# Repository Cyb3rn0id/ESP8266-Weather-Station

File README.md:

# ESP8266 Simple Weather Station

This is a simple Wi-Fi Weather Station based on a NodeMCU (ESP8266).  
It Shows Temperature, Humidity, Heat Index, Pressure, Altitude, Minimum and Maxim Temperatures on a display and on a remote device.  
I made 2 versions:  
- Server version (you connect cirectly to station IP address)
- MQTT version (you need an MQTT Broker and a system for visualize data: I use a Raspberry Pi with Mosquitto and NodeRed)

## Sensors used
- DHT22 for Temperature and Humidity
- BME280 for atmosferic pressure

In the picture I've enclosed circuit and a little 220V->5V switching PSU in an IP56 external box with transparent lid: it's made by Gewiss and box code is GW 44 426

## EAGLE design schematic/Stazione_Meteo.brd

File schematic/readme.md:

Schematic (use Eagle 8.0)
for Node MCU used please refer to my repository "Eagle Libraries"

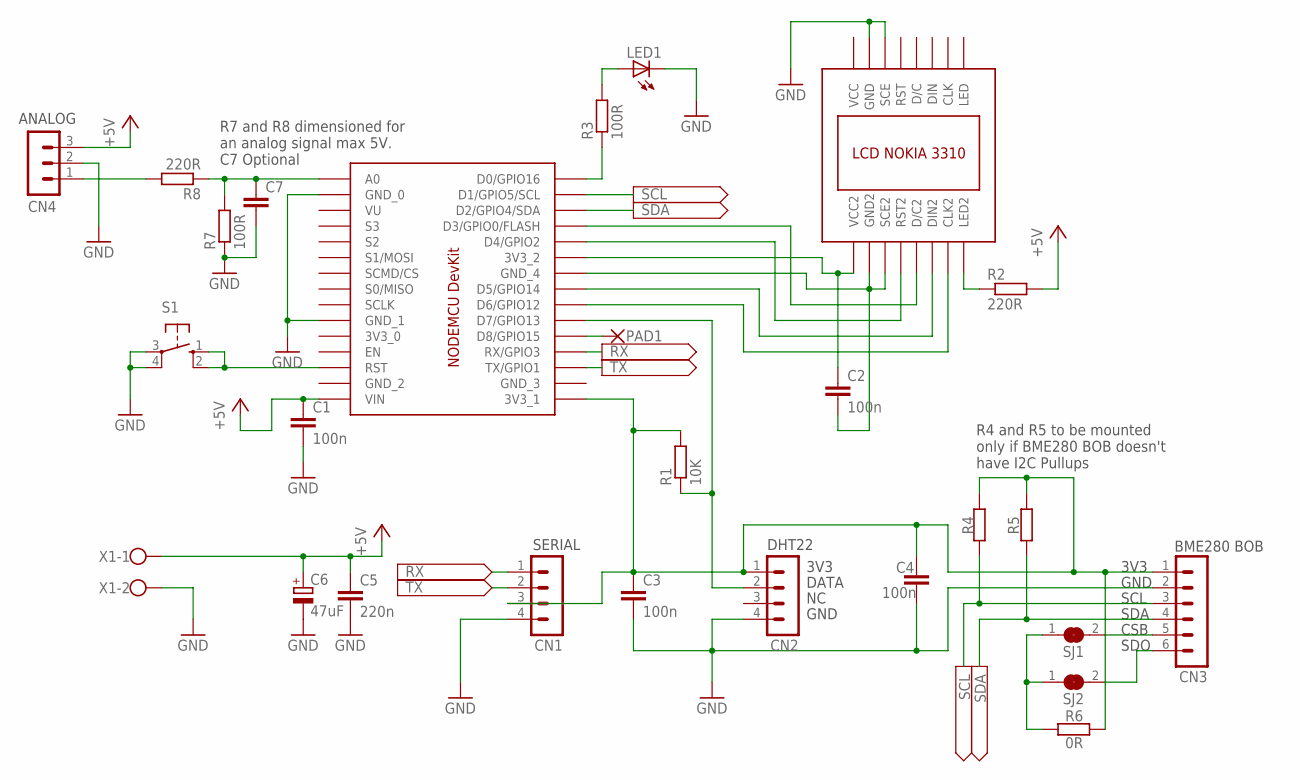
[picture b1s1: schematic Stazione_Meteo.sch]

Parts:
C1, C2, C3, C4: 100n; C025-024X044
C5: 220n; C025-024X044
C6: 47uF; E2,5-6E
C7: C-EU025-024X044; C025-024X044
CN1, CN2: MA04-1
CN3: MA06-1
CN4: MA03-1
LED1: LED5MM
PAD1: 1,6/0,9
R1: 10K; 0204/7
R2, R8: 220R; 0204/7
R3, R7: 100R; 0204/7
R4, R5: R-EU_0204/7; 0204/7
R6: 0R; 0204/7
S1: 10-XX; B3F-10XX
SJ1, SJ2: SJ
U$1: NODEMCU_DEVKIT
U$2: NOKIA_3310/5110_BOB
X1: W237-102

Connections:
3V3_0: U$1.3V3_0
+5V: C1.1, C5.1, C6.+, CN4.3, R2.2, U$1.VIN, X1.1
GND: C1.2, C3.2, C4.2, C5.2, C6.-, C7.2, CN1.4, CN2.4, CN3.2, CN4.2, LED1.K (C), R7.1, S1.3, S1.4 (P1), U$1.GND0 (GND_0), U$1.GND1 (GND_1), U$2.GND, U$2.SCE, X1.2
GND_2: U$1.GND2 (GND_2)
GND_3: U$1.GND3 (GND_3)
LED: U$2.LED
unnamed: R3.1, U$1.D0/GPIO16
unnamed: LED1.A, R3.2
unnamed: CN2.2, R1.1, U$1.D7/GPIO13
unnamed: S1.1 (S), S1.2 (S1), U$1.RST
unnamed: R2.1, U$2.LED2
unnamed: U$1.D5/GPIO14, U$2.DIN2
unnamed: U$1.D3/GPIO0 (D3/GPIO0/FLASH), U$2.D/C2
unnamed: U$1.D4/GPIO2, U$2.RST2
unnamed: C2.1, U$1.3V3_2, U$2.VCC2
unnamed: U$1.D6/GPIO12, U$2.CLK2
unnamed: R6.2, SJ1.1, SJ2.1
unnamed: C2.2, U$1.GND4 (GND_4), U$2.GND2, U$2.SCE2
unnamed: PAD1.1, U$1.D8/GPIO15
unnamed: CN3.5, SJ1.2
unnamed: CN3.6, SJ2.2
unnamed: C3.1, C4.1, CN1.3, CN2.1, CN3.1, R1.2, R4.2, R5.2, R6.1, U$1.3V3_1
unnamed: CN4.1, R8.2
unnamed: C7.1, R7.2, R8.1, U$1.A0
RX: CN1.1, U$1.RX/GPIO3
SCL: CN3.3, R4.1, U$1.D1/GPIO5 (D1/GPIO5/SCL)
SDA: CN3.4, R5.1, U$1.D2/GPIO4 (D2/GPIO4/SDA)
TX: CN1.2, U$1.TX/GPIO1
VCC: U$2.VCC

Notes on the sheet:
3V3
DATA
GND
DHT22
SCL
SDA
BME280 BOB
CSB
SDO
SERIAL
R4 and R5 to be mounted only if BME280 BOB doesn't have I2C Pullups
R7 and R8 dimensioned for an analog signal max 5V. C7 Optional
ANALOG

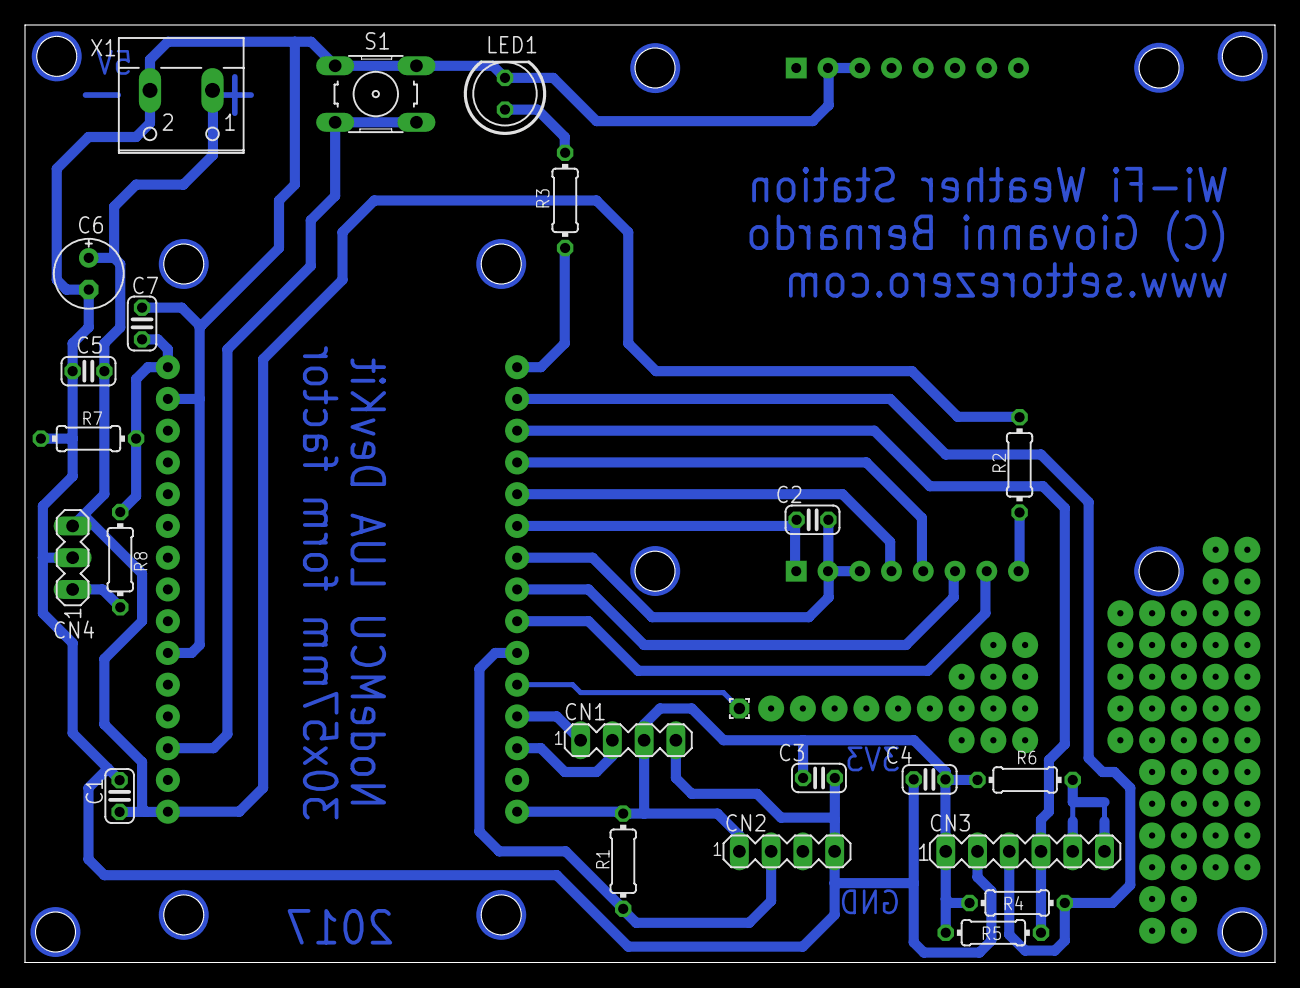
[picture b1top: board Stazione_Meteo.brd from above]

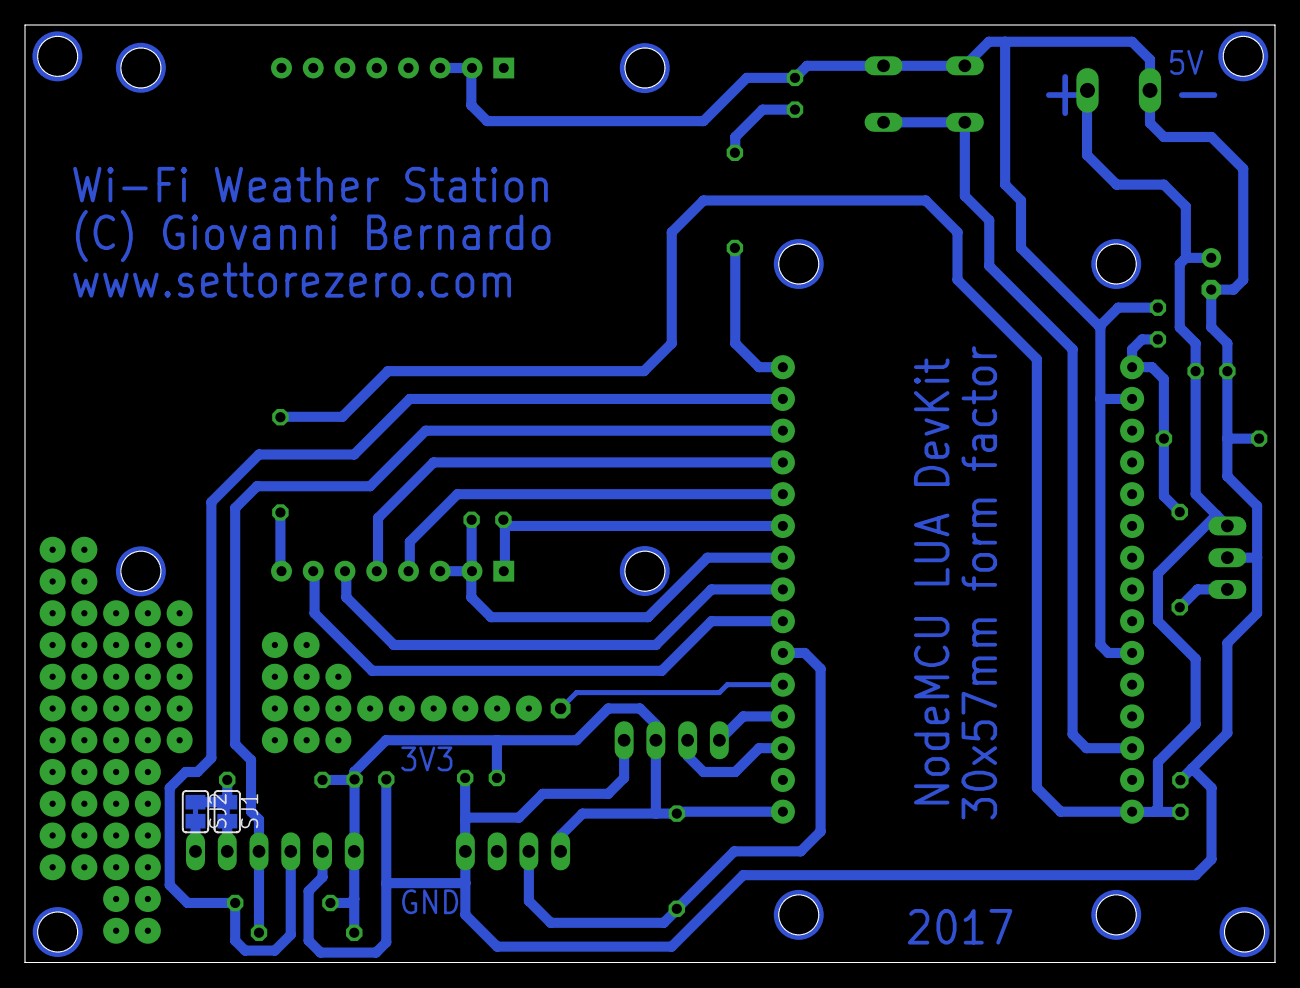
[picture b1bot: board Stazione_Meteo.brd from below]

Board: 2 copper layers, 100.0 x 75.0 mm, 27 parts (2 on the bottom side), 24 nets.

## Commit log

2017-04-16 Rename ESP8266_Meteo.ino to webpage.h
2017-04-17 Update ESP8266_Meteo.ino
    Corrected delta pressure not visualized at first attempt
    Parametrized host path for icons
    re-arranged some pieces
2017-04-17 Update webpage.h
    Parametrized host path for icons
    re-arranged some pieces of code
2017-04-18 Update ESP8266_Meteo.ino
    added "+" for delta pressure in page preload
2017-04-18 removed diode on power supply inlet
    power is +5V, diode drops 0.7V leaving available only 4.3V, not suitable for voltage regulator on NodeMCU
2018-12-31 Create ESP8266_Meteo_MQTT
